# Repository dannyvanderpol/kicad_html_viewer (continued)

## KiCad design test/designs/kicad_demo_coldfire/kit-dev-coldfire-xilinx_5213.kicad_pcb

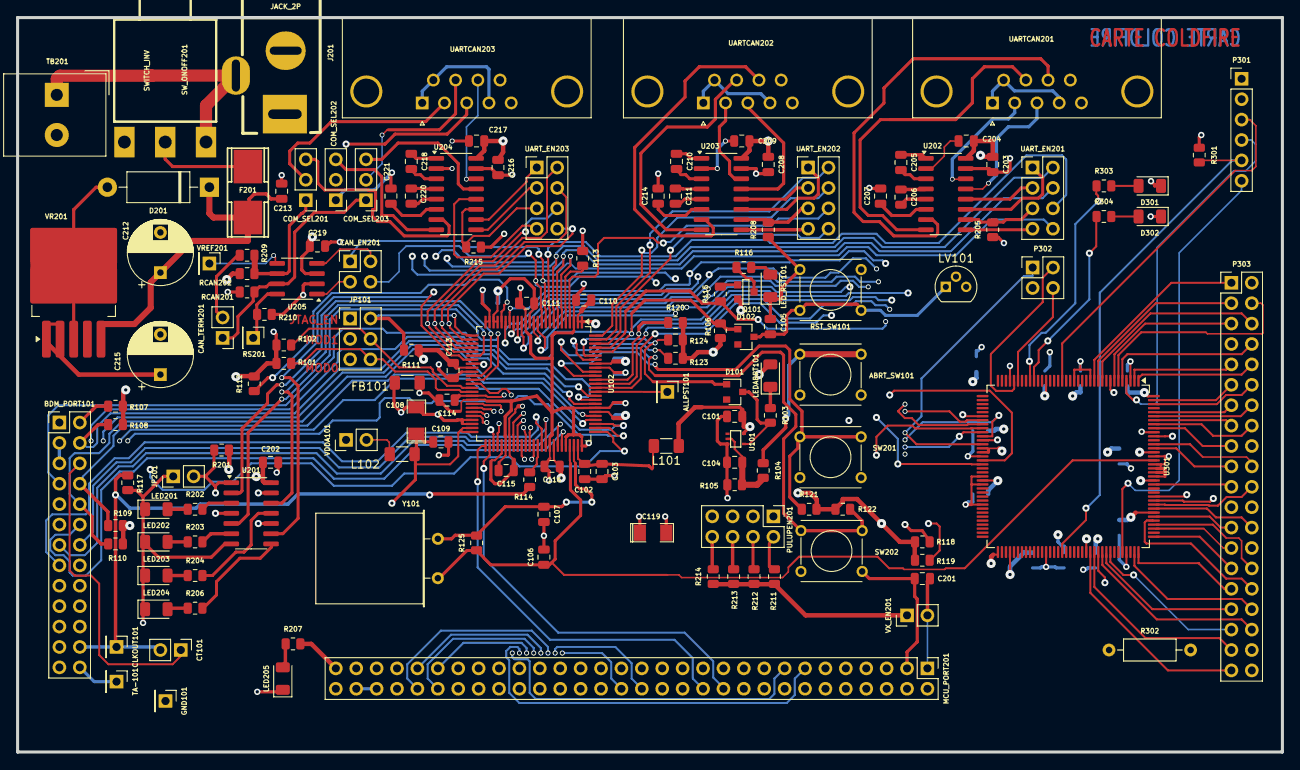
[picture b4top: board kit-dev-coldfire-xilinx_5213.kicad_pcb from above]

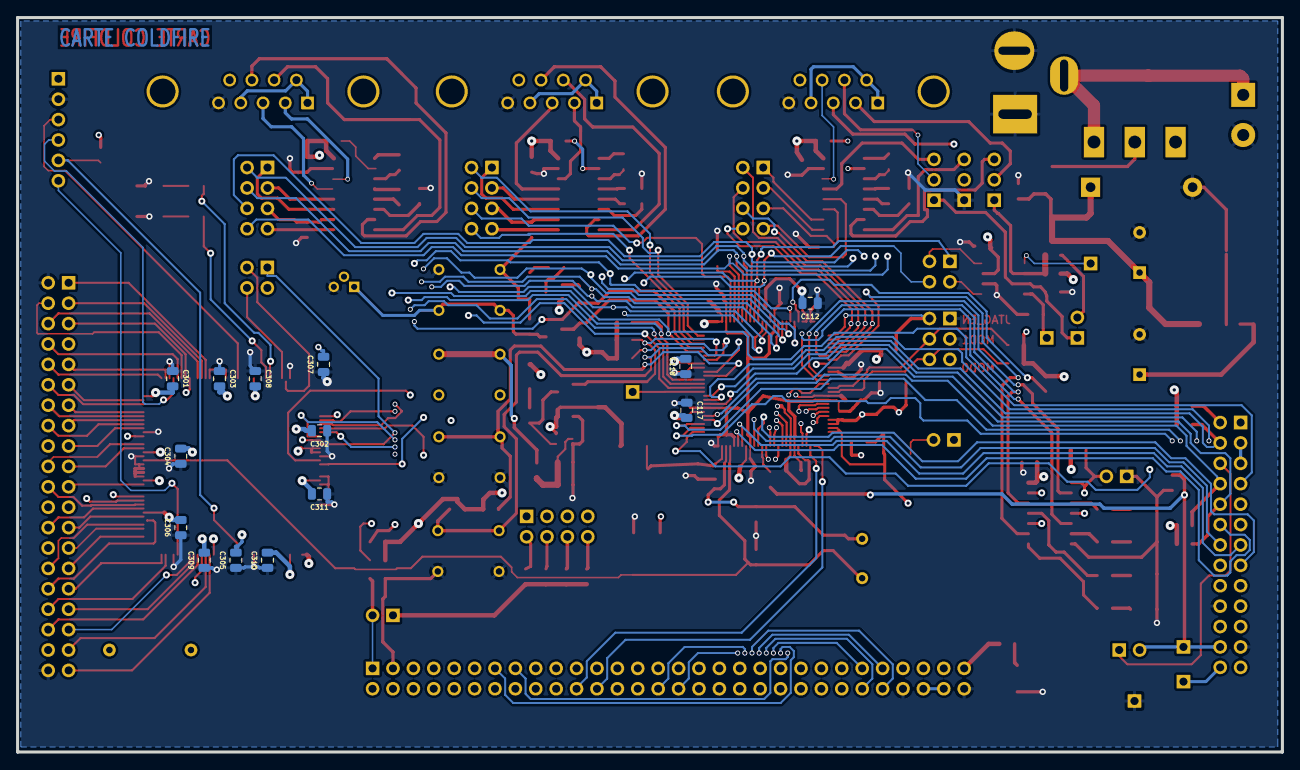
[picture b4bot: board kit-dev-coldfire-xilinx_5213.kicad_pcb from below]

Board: 4 copper layers, 157.5 x 91.4 mm, 160 parts (14 on the bottom side), 209 nets.

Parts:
ABRT_SW101: SW_PUSH; SW_PUSH_SMALL
ALLPST101: CONN_1; PinHeader_1x01_P2.54mm_Vertical
BDM_PORT101: CONN_13X2; PinHeader_2x13_P2.54mm_Vertical
C101, C103, C104, C109, C110, C111, C112, C113, C114, C115, C116, C117, C118, C201, C202, C203, C204, C205, C206, C207, C208, C209, C210, C211, C213, C214, C216, C217, C218, C219, C220, C221, C301, C302, C303, C304, C305, C306, C307, C308, C309, C310, C311: 100nF; C_0805_2012Metric
C102, C105: 1nF; C_0805_2012Metric
C106, C107: 10pF; C_0805_2012Metric
C108: 10uF; SM1206POL
C119: 100uF; SM1206POL
C212: 10uF; CP_Radial_D8.0mm_P5.00mm
C215: 220uF; CP_Radial_D8.0mm_P5.00mm
CAN_EN201: CONN_2X2; PinHeader_2x02_P2.54mm_Vertical
CAN_TERM201: JUMPER; PinHeader_1x02_P2.54mm_Vertical
CLKOUT101: CONN_1; PinHeader_1x01_P2.54mm_Vertical
COM_SEL201, COM_SEL202, COM_SEL203: CONN_3; PinHeader_1x03_P2.54mm_Vertical
CT101: JUMPER; PinHeader_1x02_P2.54mm_Vertical
D101, D102: BAT54; D_SOT-23_ANK
D201: 1N4004; D_DO-15_P12.70mm_Horizontal
D301, D302: LED; LED_1206_3216Metric
F201: FUSE; FSUPCMS
FB101: BEAD; R_1206_3216Metric_Pad1.30x1.75mm_HandSolder
GND101: CONN_1; PinHeader_1x01_P2.54mm_Vertical
J201: JACK_2P; JACK_ALIM
JP101: JUMPER_TRIPLE; PinHeader_2x03_P2.54mm_Vertical
JP201: JUMPER; PinHeader_1x02_P2.54mm_Vertical
L101, L102: 10uH; R_1206_3216Metric_Pad1.30x1.75mm_HandSolder
LED201, LED202, LED203, LED204, LED205: LED; LED_1206_3216Metric
LEDABRT101: LED_RED; LED_1206_3216Metric
LED_RST101: LED_RED; LED_1206_3216Metric
LV101: DS1818; TO-92
MCU_PORT201: CONN_30X2; PinHeader_2x30_P2.54mm_Vertical
P301: CONN_6; PinHeader_1x06_P2.54mm_Vertical
P302: CONN_2X2; PinHeader_2x02_P2.54mm_Vertical
P303: CONN_20X2; PinHeader_2x20_P2.54mm_Vertical
PULUPEN201: CONN_4X2; PinHeader_2x04_P2.54mm_Vertical
Q101: 3906; SOT23EBC
R101, R102, R106, R107, R108, R109, R110, R111, R112, R211, R212, R213, R214: 4,7K; R_0805_2012Metric
R103, R116, R202, R203, R204, R206, R207: 270; R_0805_2012Metric
R104, R210, R303, R304: 1K; R_0805_2012Metric
R105: 20K; R_0805_2012Metric
R113: 0; R_0805_2012Metric
R114: 22; R_0805_2012Metric
R115: 4.7K; R_0805_2012Metric
R117, R118, R119, R120, R121, R122, R123, R124, R201, R205, R208, R215: 10K; R_0805_2012Metric
R125: 1M; R_0805_2012Metric
R209: 62; R_0805_2012Metric
R301: 4K7; R_0805_2012Metric
R302: 3,3; R_Axial_DIN0207_L6.3mm_D2.5mm_P10.16mm_Horizontal
RCAN201, RCAN202: R; R_0805_2012Metric
RS201: CONN_1; PinHeader_1x01_P2.54mm_Vertical
RST_SW101: SW_PUSH; SW_PUSH_SMALL
SW201, SW202: SW_PUSH; SW_PUSH_SMALL
SW_ONOFF201: SWITCH_INV; SW_SPDT
TA-101: CONN_1; PinHeader_1x01_P2.54mm_Vertical
TB201: CONN_2; Altech_AK300_1x02_P5.00mm_45-Degree
U101: 74AHC1G14; SOT353
U102: MCF5213-LQFP100; LQFP-100_14x14mm_P0.5mm
U201: 74HC125; SOIC-14_3.9x8.7mm_P1.27mm
U202, U203, U204: MAX202; SOIC-16_3.9x9.9mm_P1.27mm
U205: PCA82C251; SOIC-8_3.9x4.9mm_P1.27mm
U301: XCR3256-TQ144; TQFP-144_20x20mm_P0.5mm
UARTCAN201, UARTCAN202, UARTCAN203: DB9; DSUB-9_Female_Horizontal_P2.77x2.84mm_EdgePinOffset7.70mm_H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
UART_EN201, UART_EN202, UART_EN203: CONN_4X2; PinHeader_2x04_P2.54mm_Vertical
VDDA101: JUMPER; PinHeader_1x02_P2.54mm_Vertical
VR201: LT1129_QPACK; TO-263-5_TabPin3
VREF201: CONN_1; PinHeader_1x01_P2.54mm_Vertical
VX_EN201: JUMPER; PinHeader_1x02_P2.54mm_Vertical
Y101: 8MHz; Crystal_HC18-U_Horizontal

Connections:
+3.3V: ABRT_SW101.2, BDM_PORT101.9, BDM_PORT101.25 (P24), C101.2, C110.1, C111.1, C112.1, C113.1, C114.1, C115.1, C116.1, C117.1, C118.1, C119.1, C202.1, C203.1, C204.1, C208.1, C209.1, C215.1, C216.1, C217.1, C219.1, C301.1, C302.1, C303.1, C304.1, C305.1, C306.1, C307.1, C308.1, C309.1, C310.1, C311.1, L101.1, LEDABRT101.2 (A), LV101.2 (In), MCU_PORT201.59, P301.1, Q101.1 (E), R101.1, R102.1, R106.1, R107.1, R108.1, R109.1, R110.1, R111.1, R112.2, R118.2, R119.2, R120.2, R121.2, R122.2, R123.2, R124.2, R201.1, R207.2, R211.1, R212.1, R213.1, R214.1, R301.1, R302.1, RCAN202.1, U101.5 (VCC), U102.1 (VCC), U102.2 (VCC), U102.14 (VCC), U102.22 (VCC), U102.23 (VCC), U102.34 (VCC), U102.41 (VCC), U102.55 (VSTBY), U102.57 (VCC), U102.68 (VCC), U102.81 (VCC), U102.93 (VCC), U201.14 (VCC), U202.16 (VCC), U203.16 (VCC), U204.16 (VCC), U205.3 (VCC), U301.24 (VCC), U301.50 (VCC), U301.51 (VCC), U301.58 (VCC), U301.73 (VCC), U301.76 (VCC), U301.95 (VCC), U301.115 (VCC), U301.123 (VCC), U301.130 (VCC), U301.144 (VCC), VDDA101.1, VR201.1 (OUT), VR201.2 (SENSE), VX_EN201.1
/ALLPST: ALLPST101.1, U102.86 (ALLPST)
/AN0: MCU_PORT201.10, U102.43 (AN0/PAN0)
/AN1: MCU_PORT201.12, U102.44 (AN1/PAN1)
/AN2: MCU_PORT201.14, U102.45 (AN2/PAN2)
/AN3: MCU_PORT201.16, U102.46 (AN3/PAN3)
/AN4: MCU_PORT201.18, U102.54 (AN4/PAN4)
/AN5: MCU_PORT201.20, U102.53 (AN5/PAN5)
/AN6: MCU_PORT201.22, U102.52 (AN6/PAN6)
/AN7: MCU_PORT201.24, U102.51 (AN7/PAN7)
/BKPT-: BDM_PORT101.2, R107.2, U102.76 (~BKPT/TMS)
/CANRX: CAN_EN201.4, MCU_PORT201.28, PULUPEN201.7, U102.11 (SDA/CANRX/PAS1/URXD2)
/CANTX: CAN_EN201.1, MCU_PORT201.26, PULUPEN201.5, U102.10 (SCL/CANTX/PAS0/UTXD2)
/CLKIN/EXTAL: C107.1, R125.2, U102.73 (CLKIN/EXTAL), Y101.1
/CLKMOD0: JP101.6, R101.2, U102.40 (CLKMOD0)
/CLKMOD1: JP101.4, R102.2, U102.39 (CLKMOD1)
/DDAT0: BDM_PORT101.19, U102.77 (DDATA0/PDD4)
/DDAT1: BDM_PORT101.18, U102.78 (DDATA1/PDD5)
/DDAT2: BDM_PORT101.17, U102.83 (DDATA2/PDD6)
/DDAT3: BDM_PORT101.16, U102.84 (DDATA3/PDD7)
/DSCLK: BDM_PORT101.4, R108.2, U102.85 (DSCLK/~TRST)
/DSI: BDM_PORT101.8, R109.2, U102.79 (DSI/TDI)
/DSO: BDM_PORT101.10, R110.2, U102.80 (DSO/TDO)
/DSPI_DOUT: MCU_PORT201.17, U102.17 (QSPI_DOUT/EZPQ/CANTX/RXD0/PQS0), U301.47 (M12)
/DTIN0: MCU_PORT201.34, U102.36 (DTIN0/DTOUT0/PWM0/PTC0), U201.2 (D)
/DTIN1: MCU_PORT201.36, U102.37 (DTIN1/DTOUT1/PWM2/PTC1), U201.5 (D)
/DTIN2: MCU_PORT201.38, U102.31 (DTIN2/DTOUT2/PWM4/PTC2), U201.12 (D)
/DTIN3: MCU_PORT201.40, U102.32 (DTIN3/DTOUT3/PWM6/PTC3), U201.9 (D)
/GPT0: MCU_PORT201.49, U102.58 (GPT0/PWM1/PTA0)
/GPT1: MCU_PORT201.50, U102.59 (GPT1/PWM3/PTA1)
/GPT2: MCU_PORT201.51, U102.61 (GPT2PWM5//PTA2)
/GPT3: MCU_PORT201.52, U102.62 (GPT3/PWM7/PTA3)
/IRQ-1: MCU_PORT201.2, R118.1, U102.87 (~IRQ1/PNQ1/SYNCA/PWM1), U301.42 (O2)
/IRQ-2: MCU_PORT201.8, R119.1, U102.88 (~IRQ2/PNQ2), U301.43 (O1)
/IRQ-3: MCU_PORT201.31, R120.1, U102.89 (~IRQ3/PNQ3), U301.44 (O0)
/IRQ-4: MCU_PORT201.33, R121.1, SW201.1, U102.90 (~IRQ4/PNQ4)
/IRQ-5: MCU_PORT201.35, R122.1, SW202.1, U102.91 (~IRQ5/PNQ5)
/IRQ-6: MCU_PORT201.37, R123.1, U102.94 (~IRQ6/PNQ6)
/IRQ-7: D101.2 (A), MCU_PORT201.39, R124.1, U102.95 (~IRQ7/PNQ7)
/JTAG_EN: JP101.2, R111.2, U102.26 (JTAG_EN)
/PST0: BDM_PORT101.15, U102.65 (PST0/PDD0)
/PST1: BDM_PORT101.14, U102.66 (PST1/PDD1)
/PST2: BDM_PORT101.13, U102.69 (PST2/PDD2)
/PST3: BDM_PORT101.12, U102.70 (PST3/PDD3)
/PWM1: MCU_PORT201.13, U102.38 (PWM1/PTD0)
/PWM3: MCU_PORT201.15, U102.33 (PWM3/PTD1)
/PWM5: MCU_PORT201.30, U102.60 (PWM5/PTD2)
/PWM7: MCU_PORT201.32, U102.63 (PWM7/PTD3)
/QSPI_CLK: MCU_PORT201.21, PULUPEN201.1, U102.18 (QSPI_CLK/EZPCK/SCL/RTS1/PQS2), U301.48 (M11)
/QSPI_CS0: MCU_PORT201.23, PULUPEN201.3, U102.20 (QSPI_CS0/SDA/CTS1/PQS3)
/QSPI_CS1: MCU_PORT201.25, U102.19 (QSPI_CS1/PQS4), U301.54 (M1)
/QSPI_CS2: MCU_PORT201.27, U102.13 (QSPI_CS2/PQS5), U301.45 (M15)
/QSPI_CS3: MCU_PORT201.29, U102.12 (QSPI_CS3/SYNCA/SYNCB/PQS6)
/QSPI_DIN: MCU_PORT201.19, U102.16 (QSPI_DIN/EZPD/CANRX/RXD1/PQS1), U301.46 (M13)
/RCON-: MCU_PORT201.53, R112.1, U102.21 (RCON/EZPCS)
/RSTI-: BDM_PORT101.7, D102.2 (A), MCU_PORT201.6, R106.2, U102.96 (RSTI)
/RSTO-: MCU_PORT201.4, R115.1, U102.97 (RSTO)
/TCLK: BDM_PORT101.24 (P20), CLKOUT101.1, CT101.2, R114.2, R117.1
/UCTS0: MCU_PORT201.44, U102.6 (~UCTS0/CANRX/PUA3), UART_EN201.8
/UCTS1: MCU_PORT201.11, P302.1, U102.98 (~UCTS1/SYNCA/URXD2/PUB3), U301.49 (M4), UART_EN202.8
/UCTS2: MCU_PORT201.48, U102.27 (~UCTS2/PUC3), UART_EN203.8
/URTS0: MCU_PORT201.42, U102.9 (~URTS0/CANTX/PUA2), UART_EN201.6
/URTS1: MCU_PORT201.9, P302.3, U102.4 (~URTS1/SYNCB/UTXD2/PUB2), U301.53 (M2), UART_EN202.6
/URTS2: MCU_PORT201.46, U102.30 (~URTS2/PUC2), UART_EN203.6
/URXD0: MCU_PORT201.43, U102.7 (URXD0/PUA1), UART_EN201.4
/URXD1: MCU_PORT201.7, U102.100 (URXD1/PUB1), UART_EN202.4
/URXD2: MCU_PORT201.47, U102.28 (URXD2/PUC1), UART_EN203.4
/UTXD0: MCU_PORT201.41, U102.8 (UTXD0/PUA0), UART_EN201.2
/UTXD1: MCU_PORT201.5, U102.99 (UTXD1/PUB0), UART_EN202.2
/UTXD2: MCU_PORT201.45, U102.29 (UTXD2/PUC0), UART_EN203.2
/VCCA: C108.1, C109.1, L102.2, MCU_PORT201.55, MCU_PORT201.57, U102.49 (VRH), U102.50 (VCCA)
/VDDPLL: C102.1, C103.1, L101.2, U102.74 (VCCPLL)
/XTAL: C106.1, R125.1, U102.72 (XTAL), U301.128 (CLK0/IN0), Y101.2
/inout_user/CAN_H: CAN_TERM201.1, COM_SEL203.1, RCAN201.2, U205.7 (CAN+)
/inout_user/CAN_L: COM_SEL201.1, R209.1, RCAN202.2, U205.6 (CAN-)
/inout_user/CTS0: U202.8 (R2IN), UARTCAN201.7
/inout_user/CTS1: U203.8 (R2IN), UARTCAN202.7
/inout_user/CTS2/CANH: COM_SEL203.2 (PM), UARTCAN203.7
/inout_user/RTS0: U202.7 (T2OUT), UARTCAN201.8
/inout_user/RTS1: U203.7 (T2OUT), UARTCAN202.8
/inout_user/RTS2: U204.14 (T1OUT), UARTCAN203.8
/inout_user/RXD0: U202.13 (R1IN), UARTCAN201.3
/inout_user/RXD1: U203.13 (R1IN), UARTCAN202.3
/inout_user/RXD2: COM_SEL202.2 (PM), UARTCAN203.3
/inout_user/RxD_CAN: CAN_EN201.2, U205.4 (RxD)
/inout_user/TXD0: U202.14 (T1OUT), UARTCAN201.2
/inout_user/TXD1: U203.14 (T1OUT), UARTCAN202.2
/inout_user/TXD2/CANL: COM_SEL201.2 (PM), UARTCAN203.2
/inout_user/TxD_CAN: CAN_EN201.3, U205.1 (TxD)
/xilinx/+3,3V_OUT: P303.38, R302.2
/xilinx/LED_TEST1: R303.1, U301.28 (N15)
/xilinx/LED_TEST2: R304.1, U301.27 (N14)
/xilinx/TCK: P301.5, R301.2, U301.89 (E0/TCK)
/xilinx/TDI: P301.4, U301.4 (J0/TDI)
/xilinx/TDO: P301.6, U301.104 (A2/TDO)
/xilinx/TMS: P301.3, U301.20 (N0/TMS)
/xilinx/XIL_D0: P303.1, U301.12 (L2)
/xilinx/XIL_D1: P303.3, U301.11 (J15)
/xilinx/XIL_D2: P303.5, U301.7 (J4)
/xilinx/XIL_D3: P303.7, U301.8 (J11)
/xilinx/XIL_D4: P303.9, U301.2 (I0)
/xilinx/XIL_D5: P303.11, U301.143 (I4)
/xilinx/XIL_D6: P303.13, U301.140 (I14)
/xilinx/XIL_D7: P303.15, U301.138 (K2)
/xilinx/XIL_D8: P303.17, U301.136 (K11)
/xilinx/XIL_D9: P303.19, U301.131 (K15)
/xilinx/XIL_D10: P303.21, U301.122 (D15)
/xilinx/XIL_D11: P303.23, U301.119 (D11)
/xilinx/XIL_D12: P303.25, U301.114 (D0)
/xilinx/XIL_D13: P303.27, U301.111 (B12)
/xilinx/XIL_D14: P303.29, U301.109 (B4)
/xilinx/XIL_D15: P303.31, U301.108 (B1)
/xilinx/XIL_D16: P303.33, U301.100 (A12)
/xilinx/XIL_D17: P303.35, U301.101 (A11)
/xilinx/XIL_D18: P303.37, U301.97 (C1)
/xilinx/XIL_D19: P303.39, U301.96 (C2)
/xilinx/XIL_D20: P303.4, U301.6 (J3)
/xilinx/XIL_D21: P303.6, U301.10 (J14)
/xilinx/XIL_D22: P303.8, U301.5 (J2)
/xilinx/XIL_D23: P303.10, U301.1 (I1)
/xilinx/XIL_D24: P303.12, U301.142 (I12)
/xilinx/XIL_D25: P303.14, U301.139 (I15)
/xilinx/XIL_D26: P303.16, U301.137 (K4)
/xilinx/XIL_D27: P303.18, U301.134 (K12)
/xilinx/XIL_D28: P303.20, U301.132 (K14)
/xilinx/XIL_D29: P303.22, U301.117 (D2)
/xilinx/XIL_D30: P303.24, U301.118 (D4)
/xilinx/XIL_D31: P303.26, U301.116 (D1)
/xilinx/XIL_D32: P303.28, U301.98 (C0)
/xilinx/XIL_D33: P303.30, U301.112 (B14)
/xilinx/XIL_D34: P303.32, U301.113 (B15)
/xilinx/XIL_D35: P303.34, U301.107 (B0)
/xilinx/XIL_D36: P303.36, U301.99 (A13)
GND: BDM_PORT101.3, BDM_PORT101.5, BDM_PORT101.11, BDM_PORT101.20, BDM_PORT101.23, C101.1, C102.2, C103.2, C104.2, C105.2, C106.2, C107.2, C110.2, C111.2, C112.2, C113.2, C114.2, C115.2, C116.2, C117.2, C118.2, C119.2, C201.1, C202.2, C203.2, C207.2, C208.2, C212.2, C213.2, C214.2, C215.2, C216.2, C219.2, C221.2, C301.2, C302.2, C303.2, C304.2, C305.2, C306.2, C307.2, C308.2, C309.2, C310.2, C311.2, COM_SEL202.1, D201.2 (A), D301.1 (K), D302.1 (K), FB101.1, GND101.1, J201.1, J201.2, JP101.1, JP101.3, JP101.5, JP201.1, LED201.1 (K), LED202.1 (K), LED203.1 (K), LED204.1 (K), LED205.1 (K), LED_RST101.1 (K), LV101.3 (Gbd), MCU_PORT201.3, MCU_PORT201.54, MCU_PORT201.60, P301.2, P303.2, P303.40, R105.2, R113.2, R117.2, R205.1, R208.1, R210.2, R215.1, RCAN201.1, RST_SW101.2, SW201.2, SW202.2, TB201.2 (PM), U101.3 (GND), U102.3 (GND), U102.15 (GND), U102.24 (GND), U102.25 (GND), U102.35 (GND), U102.42 (GND), U102.56 (GND), U102.67 (GND), U102.71 (GNDPLL), U102.75 (GND), U102.82 (GND), U102.92 (GND), U201.7 (GND), U202.15 (GND), U203.15 (GND), U204.15 (GND), U205.2 (GND), U301.3 (GND), U301.13 (PORT_EN), U301.17 (GND), U301.33 (GND), U301.52 (GND), U301.57 (GND), U301.59 (GND), U301.64 (GND), U301.85 (GND), U301.105 (GND), U301.124 (GND), U301.125 (CLK3/IN3), U301.126 (CLK2/IN2), U301.127 (CLK1/IN1), U301.129 (GND), U301.135 (GND), UARTCAN201.5, UARTCAN202.5, UARTCAN203.5, VR201.3 (GND)
GNDA: C108.2, C109.2, FB101.2, MCU_PORT201.56, MCU_PORT201.58, U102.47 (VSSA), U102.48 (VRL)
unnamed: ABRT_SW101.1, R104.1
unnamed: BDM_PORT101.6, CT101.1
unnamed: BDM_PORT101.26 (P22), TA-101.1
unnamed: C104.1, R104.2, R105.1, U101.2
unnamed: CAN_TERM201.2, R209.2
unnamed: COM_SEL201.3, U204.7 (T2OUT)
unnamed: COM_SEL202.3, U204.8 (R2IN)
unnamed: COM_SEL203.3, U204.13 (R1IN)
unnamed: D101.1 (K), R103.2, U101.4
unnamed: C105.1, D102.1 (K), LV101.1 (Rst), RST_SW101.1
unnamed: C212.1, C213.1, D201.1 (K), F201.2, VR201.5 (IN)
unnamed: D301.2 (A), R303.2
unnamed: D302.2 (A), R304.2
unnamed: F201.1, SW_ONOFF201.2
unnamed: L102.1, VDDA101.2
unnamed: LED201.2 (A), R202.1
unnamed: LED202.2 (A), R203.1
unnamed: LED203.2 (A), R204.1
unnamed: LED204.2 (A), R206.1
unnamed: LED205.2 (A), R207.1
unnamed: LEDABRT101.1 (K), R103.1
unnamed: LED_RST101.2 (A), R116.2
unnamed: C201.2, MCU_PORT201.1, VX_EN201.2
unnamed: PULUPEN201.2, R211.2
unnamed: PULUPEN201.4, R212.2
unnamed: PULUPEN201.6, R213.2
unnamed: PULUPEN201.8, R214.2
unnamed: Q101.2 (B), R115.2
unnamed: Q101.3 (C), R116.1
unnamed: J201.3, SW_ONOFF201.3, TB201.1
unnamed: R114.1, U102.64 (TCLK/PSTCLK/CLKOUT)
unnamed: R113.1, U102.5 (TEST)
unnamed: JP201.2, R201.2, U201.1 (E), U201.4 (E), U201.10 (E), U201.13 (E)
unnamed: R202.2, U201.3 (O)
unnamed: R203.2, U201.6 (O)
unnamed: R206.2, U201.8 (O)
unnamed: R204.2, U201.11 (O)
unnamed: C205.1, U202.1 (C1+)
unnamed: C205.2, U202.3 (C1-)
unnamed: C206.1, U202.4 (C2+)
unnamed: C206.2, U202.5 (C2-)
unnamed: U202.12 (R1OUT), UART_EN201.3
unnamed: U202.9 (R2OUT), UART_EN201.7
unnamed: U202.11 (T1IN), UART_EN201.1
unnamed: R205.2, U202.10 (T2IN), UART_EN201.5
unnamed: C204.2, U202.2 (V+)
unnamed: C207.1, U202.6 (V-)
unnamed: C210.1, U203.1 (C1+)
unnamed: C210.2, U203.3 (C1-)
unnamed: C211.1, U203.4 (C2+)
unnamed: C211.2, U203.5 (C2-)
unnamed: U203.12 (R1OUT), UART_EN202.3
unnamed: U203.9 (R2OUT), UART_EN202.7
unnamed: U203.11 (T1IN), UART_EN202.1
unnamed: R208.2, U203.10 (T2IN), UART_EN202.5
unnamed: C209.2, U203.2 (V+)
unnamed: C214.1, U203.6 (V-)
unnamed: C218.1, U204.1 (C1+)
unnamed: C218.2, U204.3 (C1-)
unnamed: C220.1, U204.4 (C2+)
unnamed: C220.2, U204.5 (C2-)
unnamed: U204.12 (R1OUT), UART_EN203.7
unnamed: U204.9 (R2OUT), UART_EN203.3
unnamed: R215.2, U204.11 (T1IN), UART_EN203.5
unnamed: U204.10 (T2IN), UART_EN203.1
unnamed: C217.2, U204.2 (V+)
unnamed: C221.1, U204.6 (V-)
unnamed: R210.1, RS201.1, U205.8 (Rsl)
unnamed: U205.5 (Vref), VREF201.1
unnamed: P302.4, U301.31 (P4)
unnamed: P302.2, U301.32 (P11)
unnamed: UARTCAN201.1, UARTCAN201.4, UARTCAN201.6
unnamed: UARTCAN202.1, UARTCAN202.4, UARTCAN202.6
unnamed: UARTCAN203.1, UARTCAN203.4, UARTCAN203.6

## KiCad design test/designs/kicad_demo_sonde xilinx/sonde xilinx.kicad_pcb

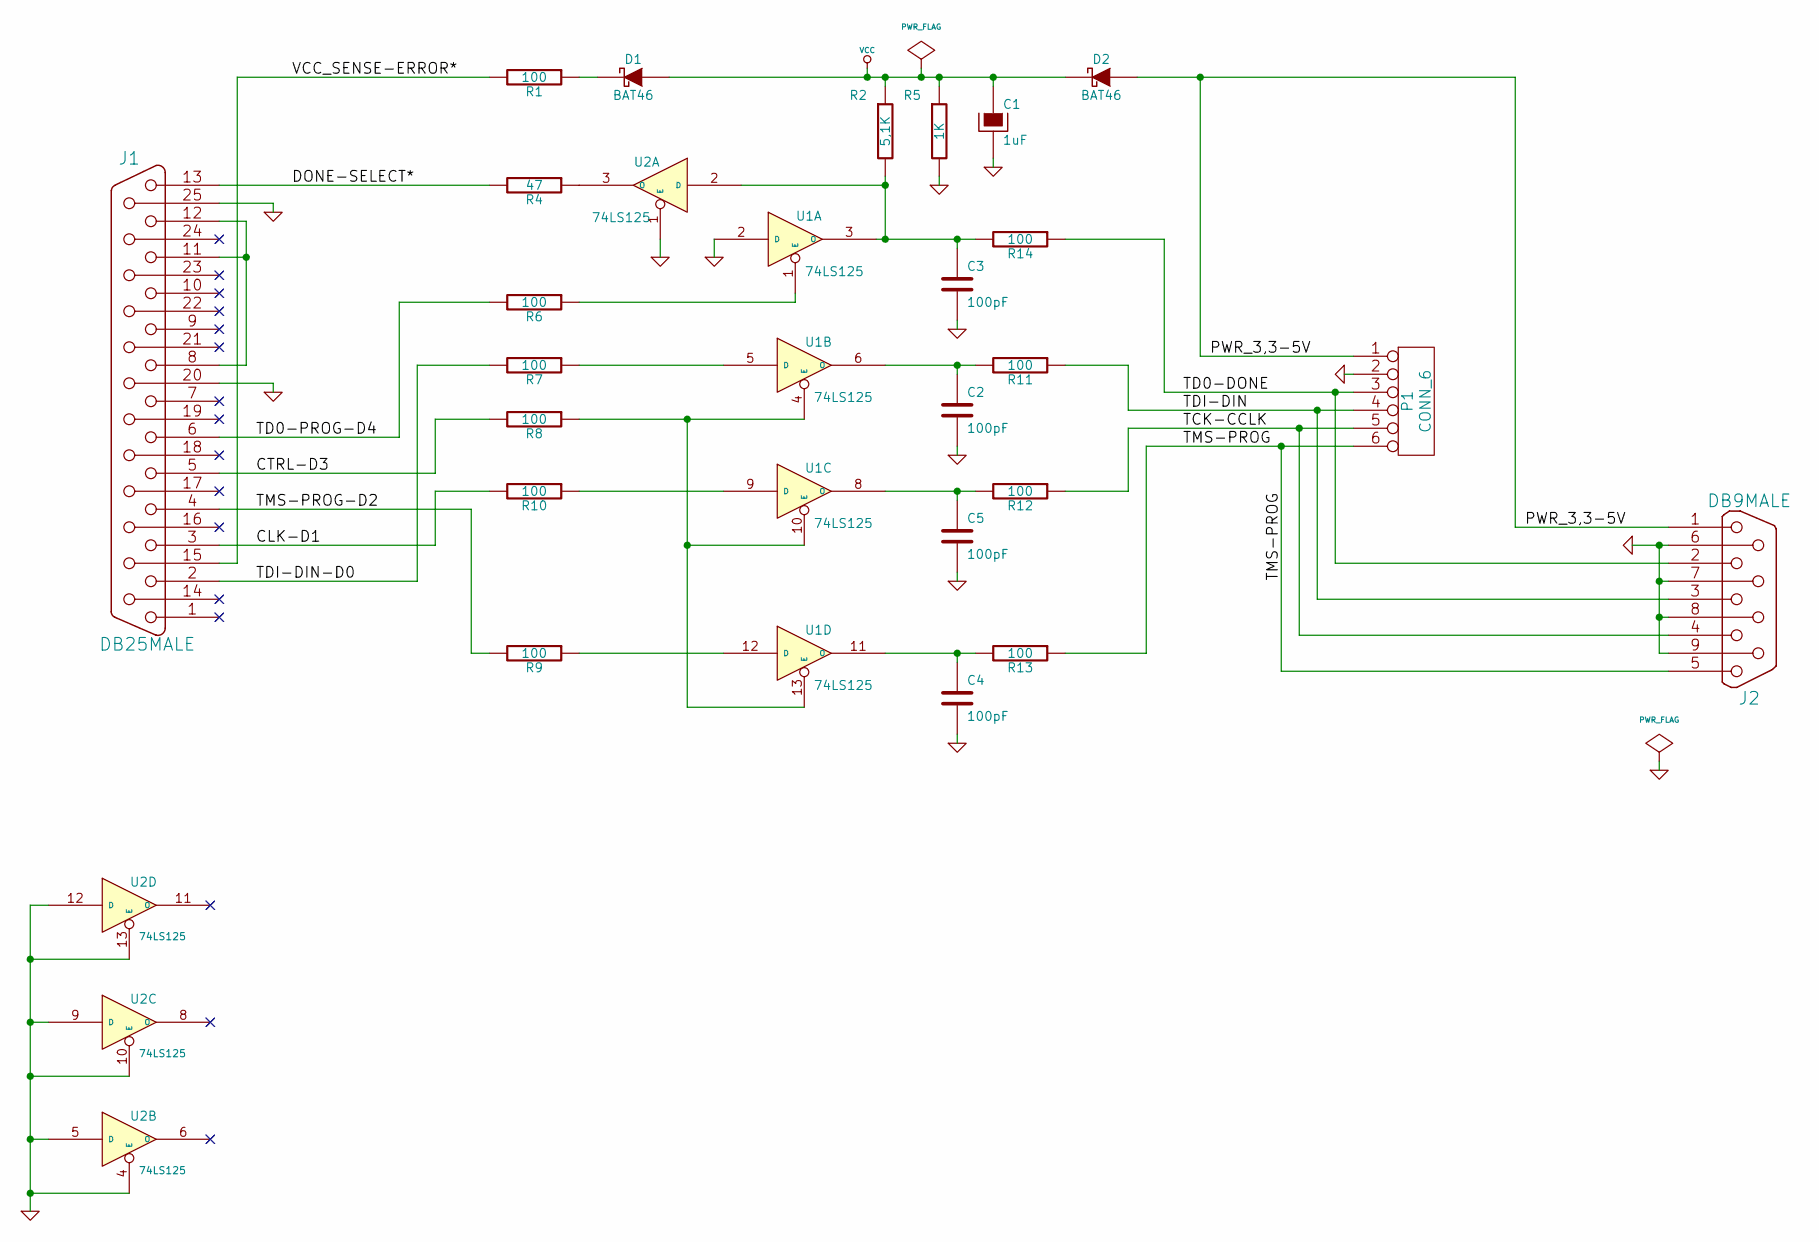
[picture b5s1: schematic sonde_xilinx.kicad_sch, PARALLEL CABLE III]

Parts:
C1: 1uF; C_Axial_L5.1mm_D3.1mm_P12.50mm_Horizontal
C2, C3, C4, C5: 100pF; C_Disc_D5.1mm_W3.2mm_P5.00mm
D1, D2: BAT46; D_A-405_P7.62mm_Horizontal
J1: DB25MALE; DSUB-25_Male_EdgeMount_P2.77mm
J2: DB9MALE; DSUB-9_Male_EdgeMount_P2.77mm
P1: CONN_6; PinHeader_1x06_P2.54mm_Vertical
R1, R6, R7, R8, R9, R10, R11, R12, R13, R14: 100; R_Axial_DIN0207_L6.3mm_D2.5mm_P10.16mm_Horizontal
R2: 5,1K; R_Axial_DIN0207_L6.3mm_D2.5mm_P10.16mm_Horizontal
R4: 47; R_Axial_DIN0207_L6.3mm_D2.5mm_P10.16mm_Horizontal
R5: 1K; R_Axial_DIN0207_L6.3mm_D2.5mm_P10.16mm_Horizontal
U1, U2: 74LS125; DIP-14_W7.62mm_LongPads

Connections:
/CLK-D1: J1.3, R10.2
/CTRL-D3: J1.5, R8.2
/DONE-SELECT*: J1.13, R4.2
/PWR_3,3-5V: D2.1 (A), J2.1, P1.1
/TCK-CCLK: J2.4, P1.5, R12.1
/TD0-DONE: J2.2, P1.3, R14.1
/TD0-PROG-D4: J1.6, R6.2
/TDI-DIN: J2.3, P1.4, R11.1
/TDI-DIN-D0: J1.2, R7.2
/TMS-PROG: J2.5, P1.6, R13.1
/TMS-PROG-D2: J1.4, R9.2
/VCC_SENSE-ERROR*: J1.15, R1.2
GND: C1.2, C2.2, C3.2, C4.2, C5.2, J1.20, J1.25, J2.6, J2.7, J2.8, J2.9, P1.2, R5.2, U1.2 (D), U1.7 (GND), U2.1 (E), U2.4 (E), U2.5 (D), U2.7 (GND), U2.9 (D), U2.10 (E), U2.12 (D), U2.13 (E)
unnamed: D1.2 (K), R1.1
unnamed: J1.8, J1.11, J1.12
unnamed: R6.1, U1.1 (E)
unnamed: C3.1, R2.2, R14.2, U1.3 (O), U2.2 (D)
unnamed: R7.1, U1.5 (D)
unnamed: R8.1, U1.4 (E), U1.10 (E), U1.13 (E)
unnamed: C2.1, R11.2, U1.6 (O)
unnamed: R10.1, U1.9 (D)
unnamed: C5.1, R12.2, U1.8 (O)
unnamed: R9.1, U1.12 (D)
unnamed: C4.1, R13.2, U1.11 (O)
unnamed: R4.1, U2.3 (O)
VCC: C1.1, D1.1 (A), D2.2 (K), R2.1, R5.1, U1.14 (VCC), U2.14 (VCC)

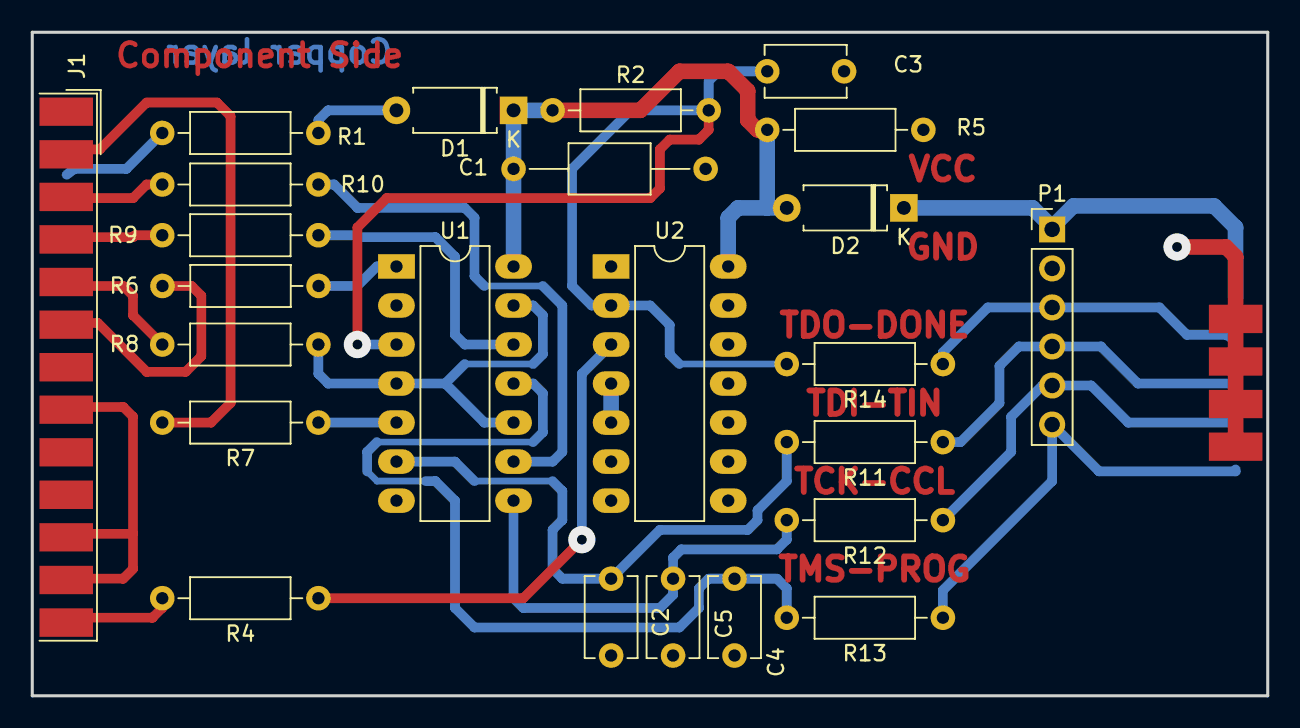
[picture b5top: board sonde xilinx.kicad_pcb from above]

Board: 2 copper layers, 80.4 x 43.2 mm, 25 parts (1 on the bottom side), 26 nets.

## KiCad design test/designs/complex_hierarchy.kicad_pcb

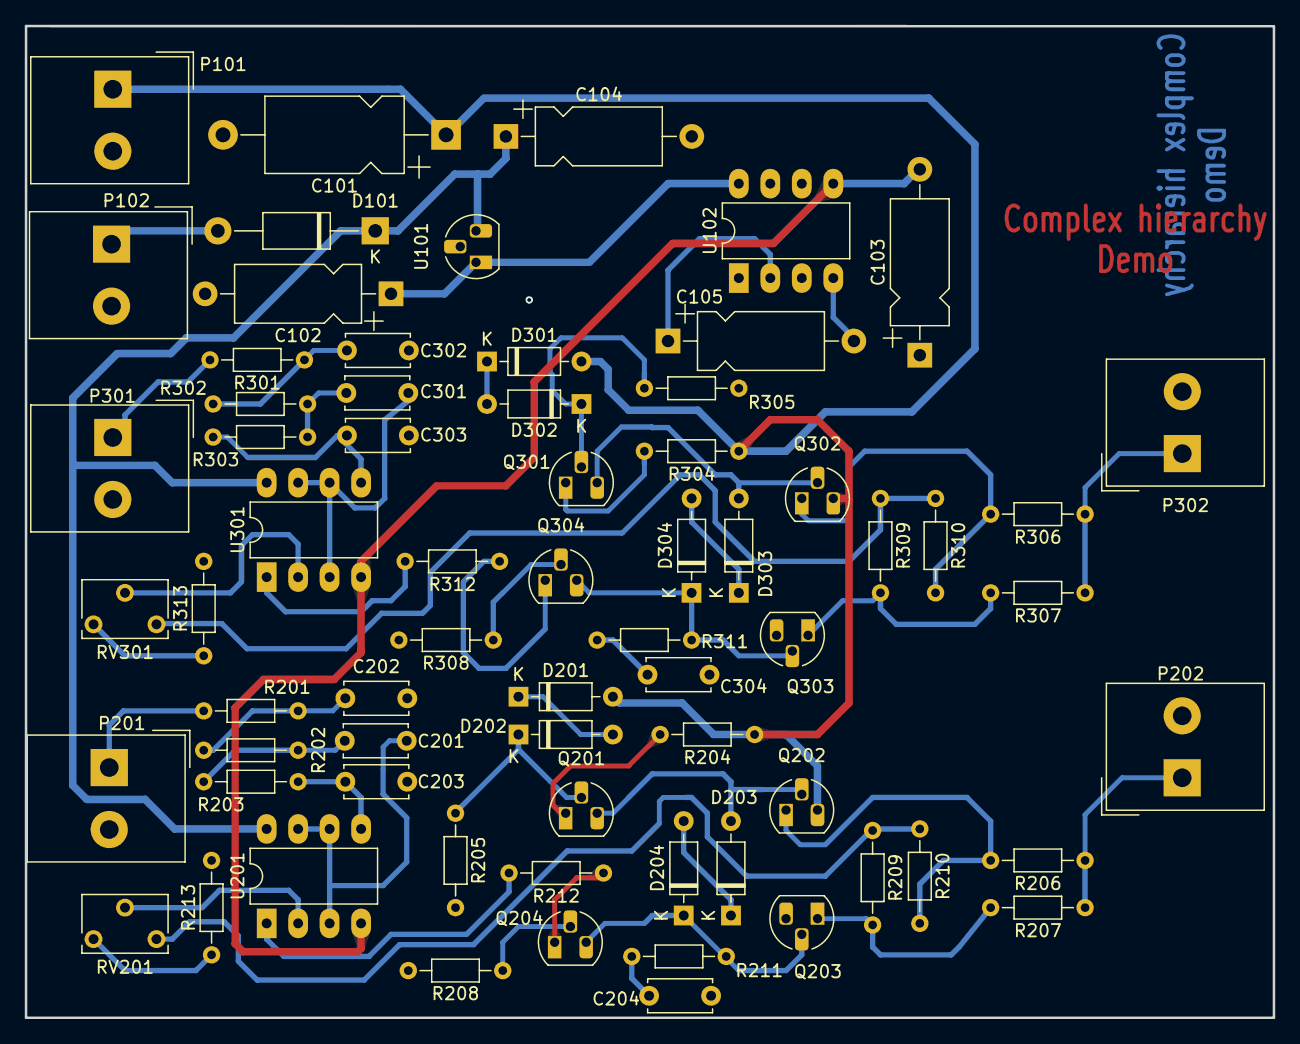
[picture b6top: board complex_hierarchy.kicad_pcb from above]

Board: 2 copper layers, 100.7 x 80.0 mm, 68 parts (0 on the bottom side), 50 nets.

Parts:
C101: 47uF/63V; CP_Axial_L11.0mm_D6.0mm_P18.00mm_Horizontal
C102: 47uF; CP_Axial_L10.0mm_D4.5mm_P15.00mm_Horizontal
C103, C105: 10uF; CP_Axial_L10.0mm_D4.5mm_P15.00mm_Horizontal
C104: 47uF/20V; CP_Axial_L10.0mm_D4.5mm_P15.00mm_Horizontal
C201, C301: 15nF; C_Disc_D5.0mm_W2.5mm_P5.00mm
C202, C302: 150nF; C_Disc_D5.0mm_W2.5mm_P5.00mm
C203, C303: 4.7nF; C_Disc_D5.0mm_W2.5mm_P5.00mm
C204, C304: 820pF; C_Disc_D5.0mm_W2.5mm_P5.00mm
D101: 1N4007; D_DO-41_SOD81_P12.70mm_Horizontal
D201, D202, D203, D204, D301, D302, D303, D304: 1N4148; D_DO-35_SOD27_P7.62mm_Horizontal
P101, P102, P201, P202, P301, P302: CONN_2; Altech_AK300_1x02_P5.00mm_45-Degree
Q201, Q203, Q301, Q303: MPSA92; TO-92_HandSolder
Q202, Q204, Q302, Q304: MPSA42; TO-92_HandSolder
R201, R208, R212, R301, R308, R312: 1K; R_Axial_DIN0204_L3.6mm_D1.6mm_P7.62mm_Horizontal
R202, R203, R302, R303: 22K; R_Axial_DIN0204_L3.6mm_D1.6mm_P7.62mm_Horizontal
R204, R304: 470; R_Axial_DIN0204_L3.6mm_D1.6mm_P7.62mm_Horizontal
R205, R209, R210, R305, R309, R310: 220K; R_Axial_DIN0204_L3.6mm_D1.6mm_P7.62mm_Horizontal
R206, R207, R306, R307: 47; R_Axial_DIN0204_L3.6mm_D1.6mm_P7.62mm_Horizontal
R211, R311: 5,6K; R_Axial_DIN0204_L3.6mm_D1.6mm_P7.62mm_Horizontal
R213, R313: 4,7K; R_Axial_DIN0204_L3.6mm_D1.6mm_P7.62mm_Horizontal
RV201, RV301: 4,7K; Potentiometer_Bourns_3266W_Vertical
U101: 78L05; TO-92_HandSolder
U102: ICL7660; DIP-8_W7.62mm_LongPads
U201, U301: LM358N; DIP-8_W7.62mm_LongPads

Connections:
+12V: C104.1, D101.1 (K), U101.3 (VI), U201.8 (V+), U301.8 (V+)
-VAA: C103.2, U102.5 (VOUT), U201.4 (V-), U301.4 (V-)
/12Vext: D101.2 (A), P102.1
/ampli_ht_horizontal/PIEZO_IN: P301.1, R301.2
/ampli_ht_horizontal/PIEZO_OUT: P302.1, R306.1, R307.1
/ampli_ht_horizontal/S_OUT+: R309.1, R310.1, RV301.3
/ampli_ht_horizontal/Vpil_0_3,3V: C301.1, U301.3 (+), U301.6 (-), U301.7
/ampli_ht_vertical/PIEZO_IN: P201.1, R201.2
/ampli_ht_vertical/PIEZO_OUT: P202.1, R206.1, R207.1
/ampli_ht_vertical/S_OUT+: R209.1, R210.1, RV201.3
/ampli_ht_vertical/Vpil_0_3,3V: C201.1, U201.3 (+), U201.6 (-), U201.7
GND: C101.2, C102.2, C103.1, C104.2, C202.2, C203.2, C204.2, C302.2, C303.2, C304.2, P101.2 (PM), P102.2 (PM), P201.2 (PM), P202.2 (PM), P301.2 (PM), P302.2 (PM), Q203.3 (C), Q303.3 (C), R205.2, R208.2, R213.2, R305.2, R308.2, R313.2, U101.2 (GND), U102.3 (GND)
HT: C101.1, D201.2 (A), D301.2 (A), P101.1, Q202.3 (C), Q302.3 (C), R204.1, R304.1
unnamed: C201.2, R202.1, R203.2
unnamed: C202.1, R201.1, R202.2
unnamed: C204.1, R211.2
unnamed: C301.2, R302.1, R303.2
unnamed: C302.1, R301.1, R302.2
unnamed: C304.1, R311.2
unnamed: D201.1 (K), D202.2 (A)
unnamed: D202.1 (K), Q201.2 (B), R205.1
unnamed: D203.2 (A), Q201.3 (C), Q202.2 (B)
unnamed: D203.1 (K), D204.2 (A)
unnamed: D204.1 (K), Q203.2 (B), Q204.3 (C), R211.1
unnamed: D301.1 (K), D302.2 (A)
unnamed: D302.1 (K), Q301.2 (B), R305.1
unnamed: D303.2 (A), Q301.3 (C), Q302.2 (B)
unnamed: D303.1 (K), D304.2 (A)
unnamed: D304.1 (K), Q303.2 (B), Q304.3 (C), R311.1
unnamed: Q201.1 (E), R204.2
unnamed: Q202.1 (E), R206.2, R210.2
unnamed: Q203.1 (E), R207.2, R209.2
unnamed: Q204.2 (B), R208.1
unnamed: Q204.1 (E), R212.1
unnamed: Q301.1 (E), R304.2
unnamed: Q302.1 (E), R306.2, R310.2
unnamed: Q303.1 (E), R307.2, R309.2
unnamed: Q304.2 (B), R308.1
unnamed: Q304.1 (E), R312.1
unnamed: R212.2, U201.1
unnamed: R213.1, RV201.1
unnamed: R312.2, U301.1
unnamed: R313.1, RV301.1
unnamed: C105.1, U102.2 (CAP+)
unnamed: C105.2, U102.4 (CAP-)
unnamed: RV201.2, U201.2 (-)
unnamed: C203.1, R203.1, U201.5 (+)
unnamed: RV301.2, U301.2 (-)
unnamed: C303.1, R303.1, U301.5 (+)
VCC: C102.1, U101.1 (VO), U102.8 (V+)

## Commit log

2025-12-04 Change filename
2025-12-04 file renamed
2025-12-04 add VS code work space
2025-12-04 add temporary files to git ignore
2025-12-04 add skeleton and test page
2025-12-04 add reader skeleton
2025-12-04 add load content from URL
2025-12-04 reading sections from a KiCad file
2025-12-04 default value for content type
2025-12-04 add remark about supported versions
2025-12-04 add loading default page layout
2025-12-05 load page layout from JS file, no external file needed
2025-12-05 renamed file
2025-12-05 add drawer skeleton
2025-12-05 renamed function
2025-12-05 add KiColors object
2025-12-05 read paper size from design
2025-12-05 draw page outline
2025-12-05 read setup section
2025-12-05 add setup to the drawer
2025-12-05 updated file descriptions
2025-12-05 add read lines and rectangles
2025-12-05 draw sheet outlines
2025-12-05 using correct values from setup
2025-12-07 add parsing title block text properties
2025-12-07 simplified colors for worksheet (always the same color)
2025-12-07 draw text
2025-12-07 add h/v alognment and mirror
2025-12-07 add debug level for colors
2025-12-07 add pan and zoom
2025-12-08 Add newstroke font (similar to KiCad font)
2025-12-08 add keep page inside the view
2025-12-08 separate X and Y scaling
2025-12-08 fit page to width of height depending on ratio
2025-12-08 change canvas size
2025-12-08 removed debug message
2025-12-08 correct Y for texts
2025-12-08 add workflow for bundle and minify
2025-12-08 updated to latest versions
2025-12-08 updated workflow
2025-12-08 fixed indentation
2025-12-08 updated run command
2025-12-08 fixed typo in name
2025-12-08 add git add command
2025-12-08 Updated build
2025-12-08 add test page for build and source
2025-12-08 add example page
2025-12-08 add build badge
2025-12-08 skip commit if there are no changes
2025-12-08 fix if else block
2025-12-09 change quotes
2025-12-09 moved file to sub folder
2025-12-09 generate pagelayout JS
2025-12-09 parse values for title block
2025-12-09 updated doc string
2025-12-09 add parsing and drawing junctions
2025-12-09 skip reading embedded fonts
2025-12-09 Updated text in the web pages
2025-12-09 typo in file name
2025-12-09 read and draw zones, has bug
2025-12-10 fixed drawing polygons for zones
2025-12-10 typo
2025-12-10 fix reading zones
2025-12-10 removed debug log
2025-12-10 Fix drawing circles
2025-12-10 moved file
2025-12-10 add new parser object (empty)
2025-12-11 add fetch file function in lib
2025-12-11 add design object
2025-12-11 add parser function
2025-12-11 add new parser function
2025-12-12 add global logger
2025-12-12 use global logger
2025-12-12 updated log formatting
2025-12-12 can only 1 decimal accurate
2025-12-12 removed timing functions
2025-12-12 add sections parser
2025-12-12 parse main section
2025-12-13 Update name and email for workflow
    Updated the email and name used for git configuration in the workflow.
2025-12-13 add log level for timer
2025-12-13 add timer module
2025-12-13 add time processes and show report
2025-12-13 store time as rounded number, not as string
2025-12-13 add time process
2025-12-13 move font to lib
2025-12-13 change label for timer
2025-12-13 use new design object
2025-12-13 add graphics object class
2025-12-13 add base parser
2025-12-13 updated timer label
2025-12-13 add polygons for zones
2025-12-13 add parsing sub sections
2025-12-13 removed old stuff
2025-12-13 move time measurement to fetch file function
2025-12-13 track every call for a lable
2025-12-13 add kip parsin embedded fonts
2025-12-13 add design element object
2025-12-13 using new design object
2025-12-13 renamed class and file
2025-12-13 removed old JS files
2025-12-13 set filename for design object
2025-12-13 add drawer class
2025-12-13 add log levels
2025-12-13 add layer property
2025-12-13 add drawer levels
2025-12-13 change attribute name
2025-12-13 add drawing elements
2025-12-13 add filename to design object
2025-12-13 updated the way to load the font
2025-12-13 add page layout object to lib
2025-12-13 Add comment about the source of the page layout
2025-12-13 updated header format
2025-12-13 fix wrong quotes used
2025-12-13 passing canvas context to drawer
2025-12-13 show warning when some layers are not drawn
2025-12-13 default layer to 'design'
2025-12-13 add calling draw element function
2025-12-13 add check for points before drawing
2025-12-13 implement drawing polygon
2025-12-13 add colors object
2025-12-13 use default color for graphics elements
2025-12-13 add level for color parser
2025-12-13 add parsin layer and points for zones
2025-12-13 add colors for copper layers
2025-12-13 fix setting default settings
2025-12-13 add copper layer to layer order
2025-12-13 add parsing color
2025-12-13 disable logging output
2025-12-13 fix correct objects
2025-12-13 add parsing values and properties
2025-12-13 Add features section to README
    Added a features section to the README with details about drawing designs and PCB functionality.
2025-12-13 Update features and roadmap
    Added pan and zoom functionality to features list and updated roadmap.
2025-12-13 add screenshot of the PCB
2025-12-13 add border trick to image
2025-12-14 split up parse file
2025-12-14 add page layout elements
2025-12-14 add correct logger
2025-12-14 add design page element
2025-12-14 parsing paper size
2025-12-14 fix correct reference
2025-12-14 add fit page to viewport on init
2025-12-14 add log level for parse element
2025-12-14 get design element by reference
2025-12-14 refactored handling parsers
2025-12-14 add reference field to design element
2025-12-14 set minimum points depending on graphics type
2025-12-14 add rectangle class
2025-12-14 if no sections found just parse the section content
2025-12-14 add paper parser
2025-12-14 updated screenshot
2025-12-14 Update features list
2025-12-15 add scaled thickness for paper outline
2025-12-15 add parsing the setup
2025-12-15 parsing generator version
2025-12-15 add background color
2025-12-15 fix drawing rectangle
2025-12-15 add colros for worksheet
2025-12-15 class renamed
2025-12-15 fix proper name for setup element
2025-12-15 add parsing rectangle sections
2025-12-15 updated screenshots
2025-12-16 add console area for log messages
2025-12-16 update logger to use console messages
2025-12-16 create report for new logger
2025-12-16 using new logger
2025-12-16 add colors to the log levels
2025-12-16 simplified log levels
2025-12-16 set correct log levels
2025-12-16 updated logger levels
2025-12-16 don't log skipped fiels for zone (too many logs)
2025-12-16 Using settime to update the console view and prevent browser freezes
2025-12-16 updated log messages
2025-12-16 setup log levels
2025-12-17 add logging area
2025-12-17 set default log level in the logger class
2025-12-17 increase the height of the console
2025-12-17 add option for user settings though HTML page
2025-12-17 only minify syntax
2025-12-17 bundle only (no minify)
2025-12-17 minify whitespace only
2025-12-17 add comment about minify
2025-12-18 add parsing lines
2025-12-18 change parameter for parsing is always the section content
2025-12-18 change property thickness to size
2025-12-18 add parsing text
2025-12-18 updated screen shots
2025-12-19 fix save image includes the background color
2025-12-19 add key value map for replacing keys in text
2025-12-19 parsing title block
2025-12-19 add paper size to the key value map
2025-12-19 add default page numbers
2025-12-19 removed debug output
2025-12-19 add parsing and drawing segments
2025-12-19 set default composite operation
2025-12-19 fix did not set the correct layer for the lines
2025-12-19 skip parsin nets (for now)
2025-12-19 add via for testing vias
2025-12-20 fix handling error when file does not exist
2025-12-20 use other design for testing
2025-12-20 fix the design was not set correct
2025-12-20 add KiCad non project files to git ignore
2025-12-20 log out put same width as canvas
2025-12-20 change the location of the screenshots
2025-12-20 refactored common CSS for both test pages
2025-12-20 refactor put common stuf for test page in common file
2025-12-20 add local test settings (not in git)
2025-12-20 use local test settings
2025-12-20 add logging for events
2025-12-21 add reading embedded worksheet
2025-12-21 skip parsing uuid
2025-12-21 renamed project
2025-12-21 add some KiCad demo prohects to play with
2025-12-21 files renamed
2025-12-21 add selecting project and log level to the test page
2025-12-21 removed some logging (slowing down too much)
2025-12-21 define default PCB alpha in Colors lib
2025-12-21 Parsing and drawing layers from the design
2025-12-21 update text about screenshots
2025-12-21 move file to docs\build
2025-12-21 add deploy pages work flow
2025-12-21 add index HTL anad cookies JS to docs
2025-12-21 folder renamed
2025-12-21 build output to pages
2025-12-21 update path to build
2025-12-21 update folder for build file
2025-12-21 Add badge for deploy pages
2025-12-21 fix badge
2025-12-21 Add linkt to the github pages
2025-12-22 moved test pages to pages folder
2025-12-22 updated links to project and removed not working project
2025-12-22 fix reading from base64 encoded data
2025-12-22 changed location of screenshots
2025-12-23 add color override
2025-12-23 add setting log level for test page
2025-12-23 set design element to null as default
2025-12-23 add support pages in portrait
2025-12-23 add parsing and drawinf wires
2025-12-23 removed unused import
2025-12-23 fix junction size (radius vs diameter)
2025-12-23 add counting code lines
2025-12-24 ad parsing and draawing busses
2025-12-24 add parse and draw bus entries
2025-12-24 removed properties
2025-12-25 add bus entry parser
2025-12-25 add junction parser
2025-12-25 added logic for selecting the proper parser
2025-12-25 add tb parser
2025-12-25 fixed issue if page is not available
2025-12-25 renamed junction to circle
2025-12-25 updated comment
2025-12-25 add setup parser
2025-12-25 add embedded files parser
2025-12-25 get element parser from structure
2025-12-25 add title block parser
2025-12-25 add sheet name key
2025-12-25 moved element parser into a subfolder
2025-12-25 skip embedded fonts
2025-12-25 fix error when no cookie was set
2025-12-25 add skip version and generator sections
2025-12-25 add reading version and uuid
2025-12-25 add line parser
2025-12-25 add wire parser
2025-12-25 fix handle margins and paper size when not set
2025-12-25 add rectangle parser
2025-12-25 made comments more consistent
2025-12-25 remove old parsers
2025-12-25 add layers parser
2025-12-25 add zone parser
2025-12-25 add small delay in writng log messages
2025-12-25 add segment parser
2025-12-25 add fill color to rectangle
2025-12-25 add prsing and drawing sheet outline
2025-12-25 increased size of canvas to match console
2025-12-25 remove requirement for using substring
2025-12-25 fix removed substring, not needed
2025-12-26 fixed parsing values
2025-12-26 add parse sheet name and filename
2025-12-26 add parsing sheet pins
2025-12-27 add parsing sheet pins labels
2025-12-27 removed debug print
2025-12-27 add parse bus
2025-12-27 add statistics
